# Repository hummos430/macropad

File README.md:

A render of the Macropad

SS of the PCB Schematic

SS of the PCB Layout

3d view of case

## Components

| Part | Cost |
|---|---|
| Seeed Studio XIAO RP2040 | ~$6 |
| Cherry MX Switches (x4) | ~$3 |
| Rotary Encoder | ~$2 |
| SSD1306 OLED Display | ~$4 |
| PCB (JLCPCB, 5 pack) | ~$5 |
| 3D Printed Case | ~$3 |
| M3 Screws and Heatset Inserts | ~$1 |
| **Total** | **~$24** |

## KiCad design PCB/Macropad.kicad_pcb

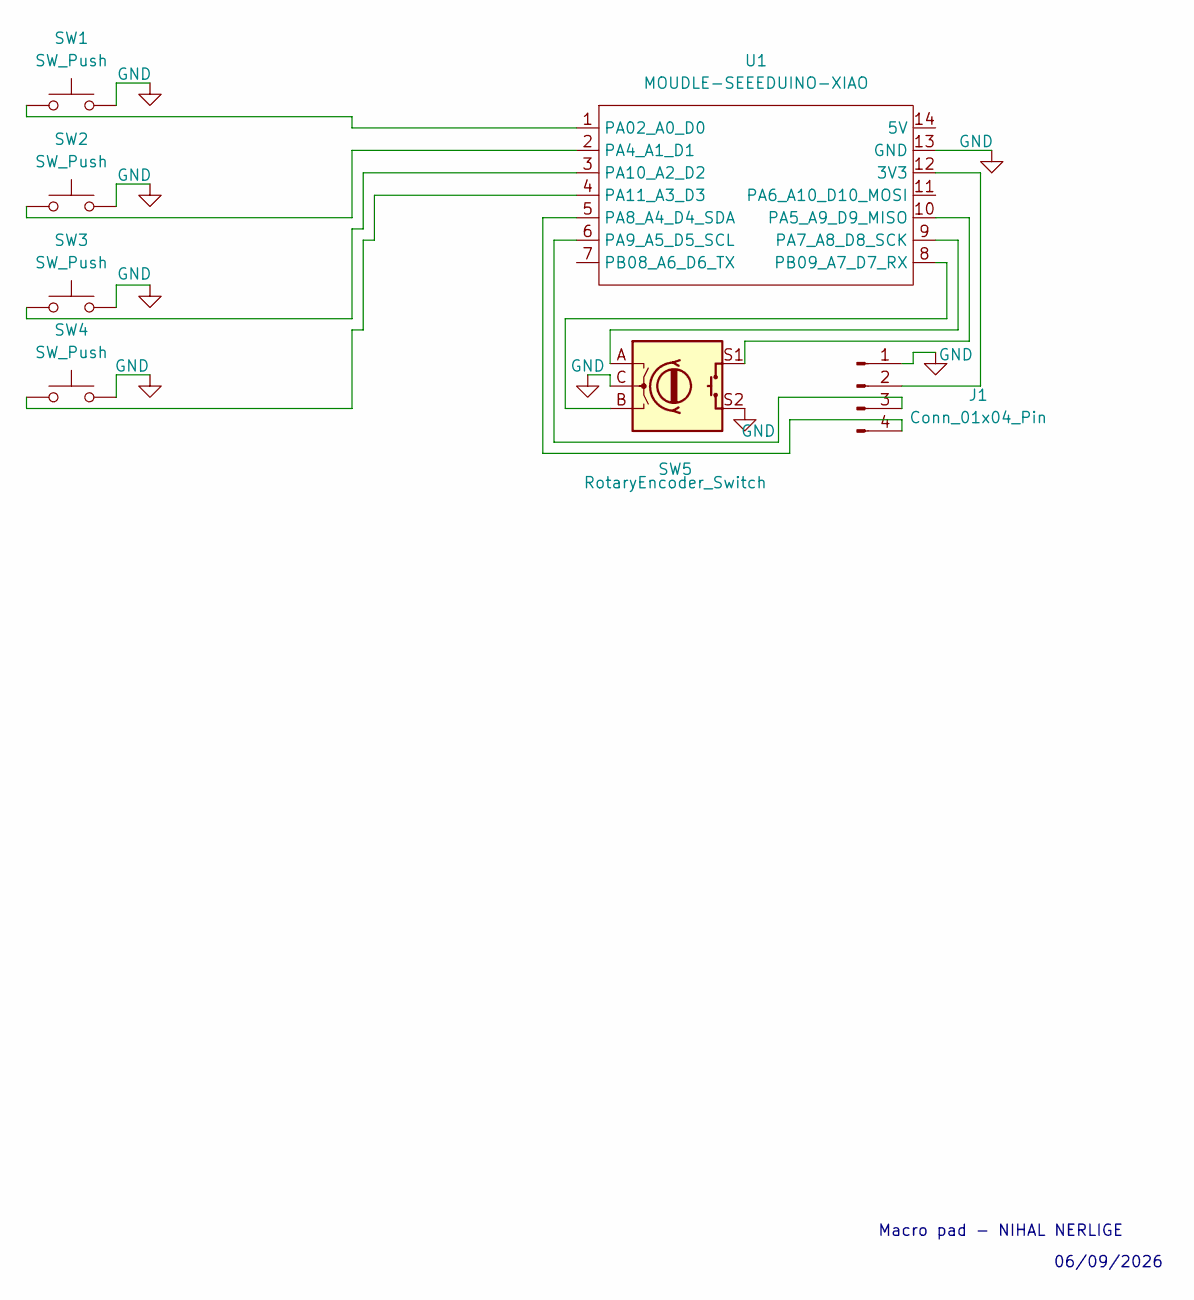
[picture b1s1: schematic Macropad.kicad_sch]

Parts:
J1: Conn_01x04_Pin; PinHeader_1x04_P2.54mm_Vertical
SW1, SW2, SW3, SW4: SW_Push; SW_Cherry_MX_1.00u_PCB
SW5: RotaryEncoder_Switch; RotaryEncoder_Alps_EC11E-Switch_Vertical_H20mm
U1: MOUDLE-SEEEDUINO-XIAO; XIAO-Generic-Hybrid-14P-2.54-21X17.8MM

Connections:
GND: J1.1, SW1.2, SW2.2, SW3.2, SW4.2, SW5.C, SW5.S2, U1.13 (GND)
unnamed: J1.2, U1.12 (3V3)
unnamed: J1.3, U1.6 (PA9_A5_D5_SCL)
unnamed: J1.4, U1.5 (PA8_A4_D4_SDA)
unnamed: SW1.1, U1.1 (PA02_A0_D0)
unnamed: SW2.1, U1.2 (PA4_A1_D1)
unnamed: SW5.S1, U1.10 (PA5_A9_D9_MISO)
unnamed: SW5.A, U1.9 (PA7_A8_D8_SCK)
unnamed: SW3.1, U1.3 (PA10_A2_D2)
unnamed: SW4.1, U1.4 (PA11_A3_D3)
unnamed: SW5.B, U1.8 (PB09_A7_D7_RX)

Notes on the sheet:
06/09/2026
Macro pad - NIHAL NERLIGE

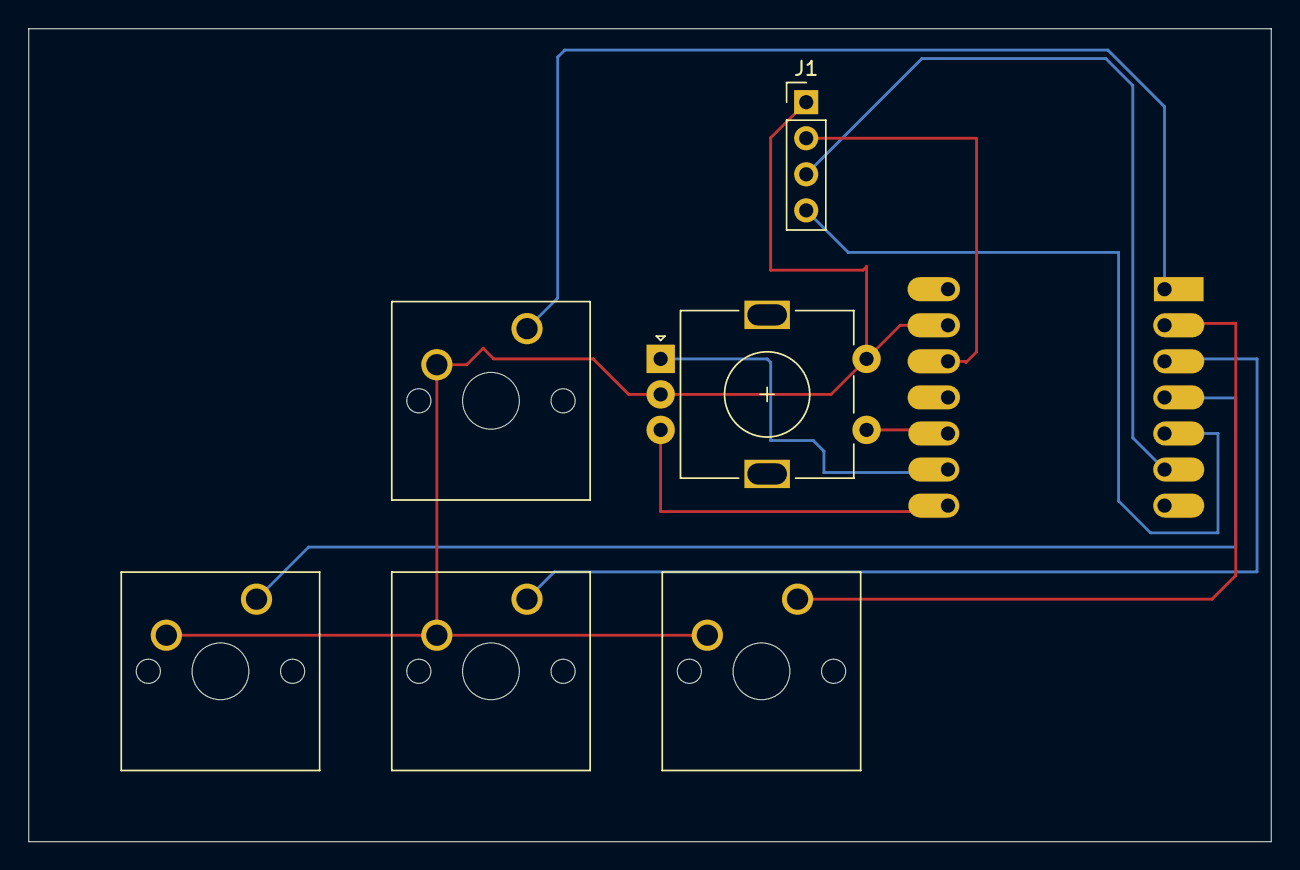
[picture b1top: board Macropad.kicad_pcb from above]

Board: 2 copper layers, 87.5 x 57.2 mm, 7 parts (1 on the bottom side), 11 nets.

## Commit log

2026-06-13 Create macropad
